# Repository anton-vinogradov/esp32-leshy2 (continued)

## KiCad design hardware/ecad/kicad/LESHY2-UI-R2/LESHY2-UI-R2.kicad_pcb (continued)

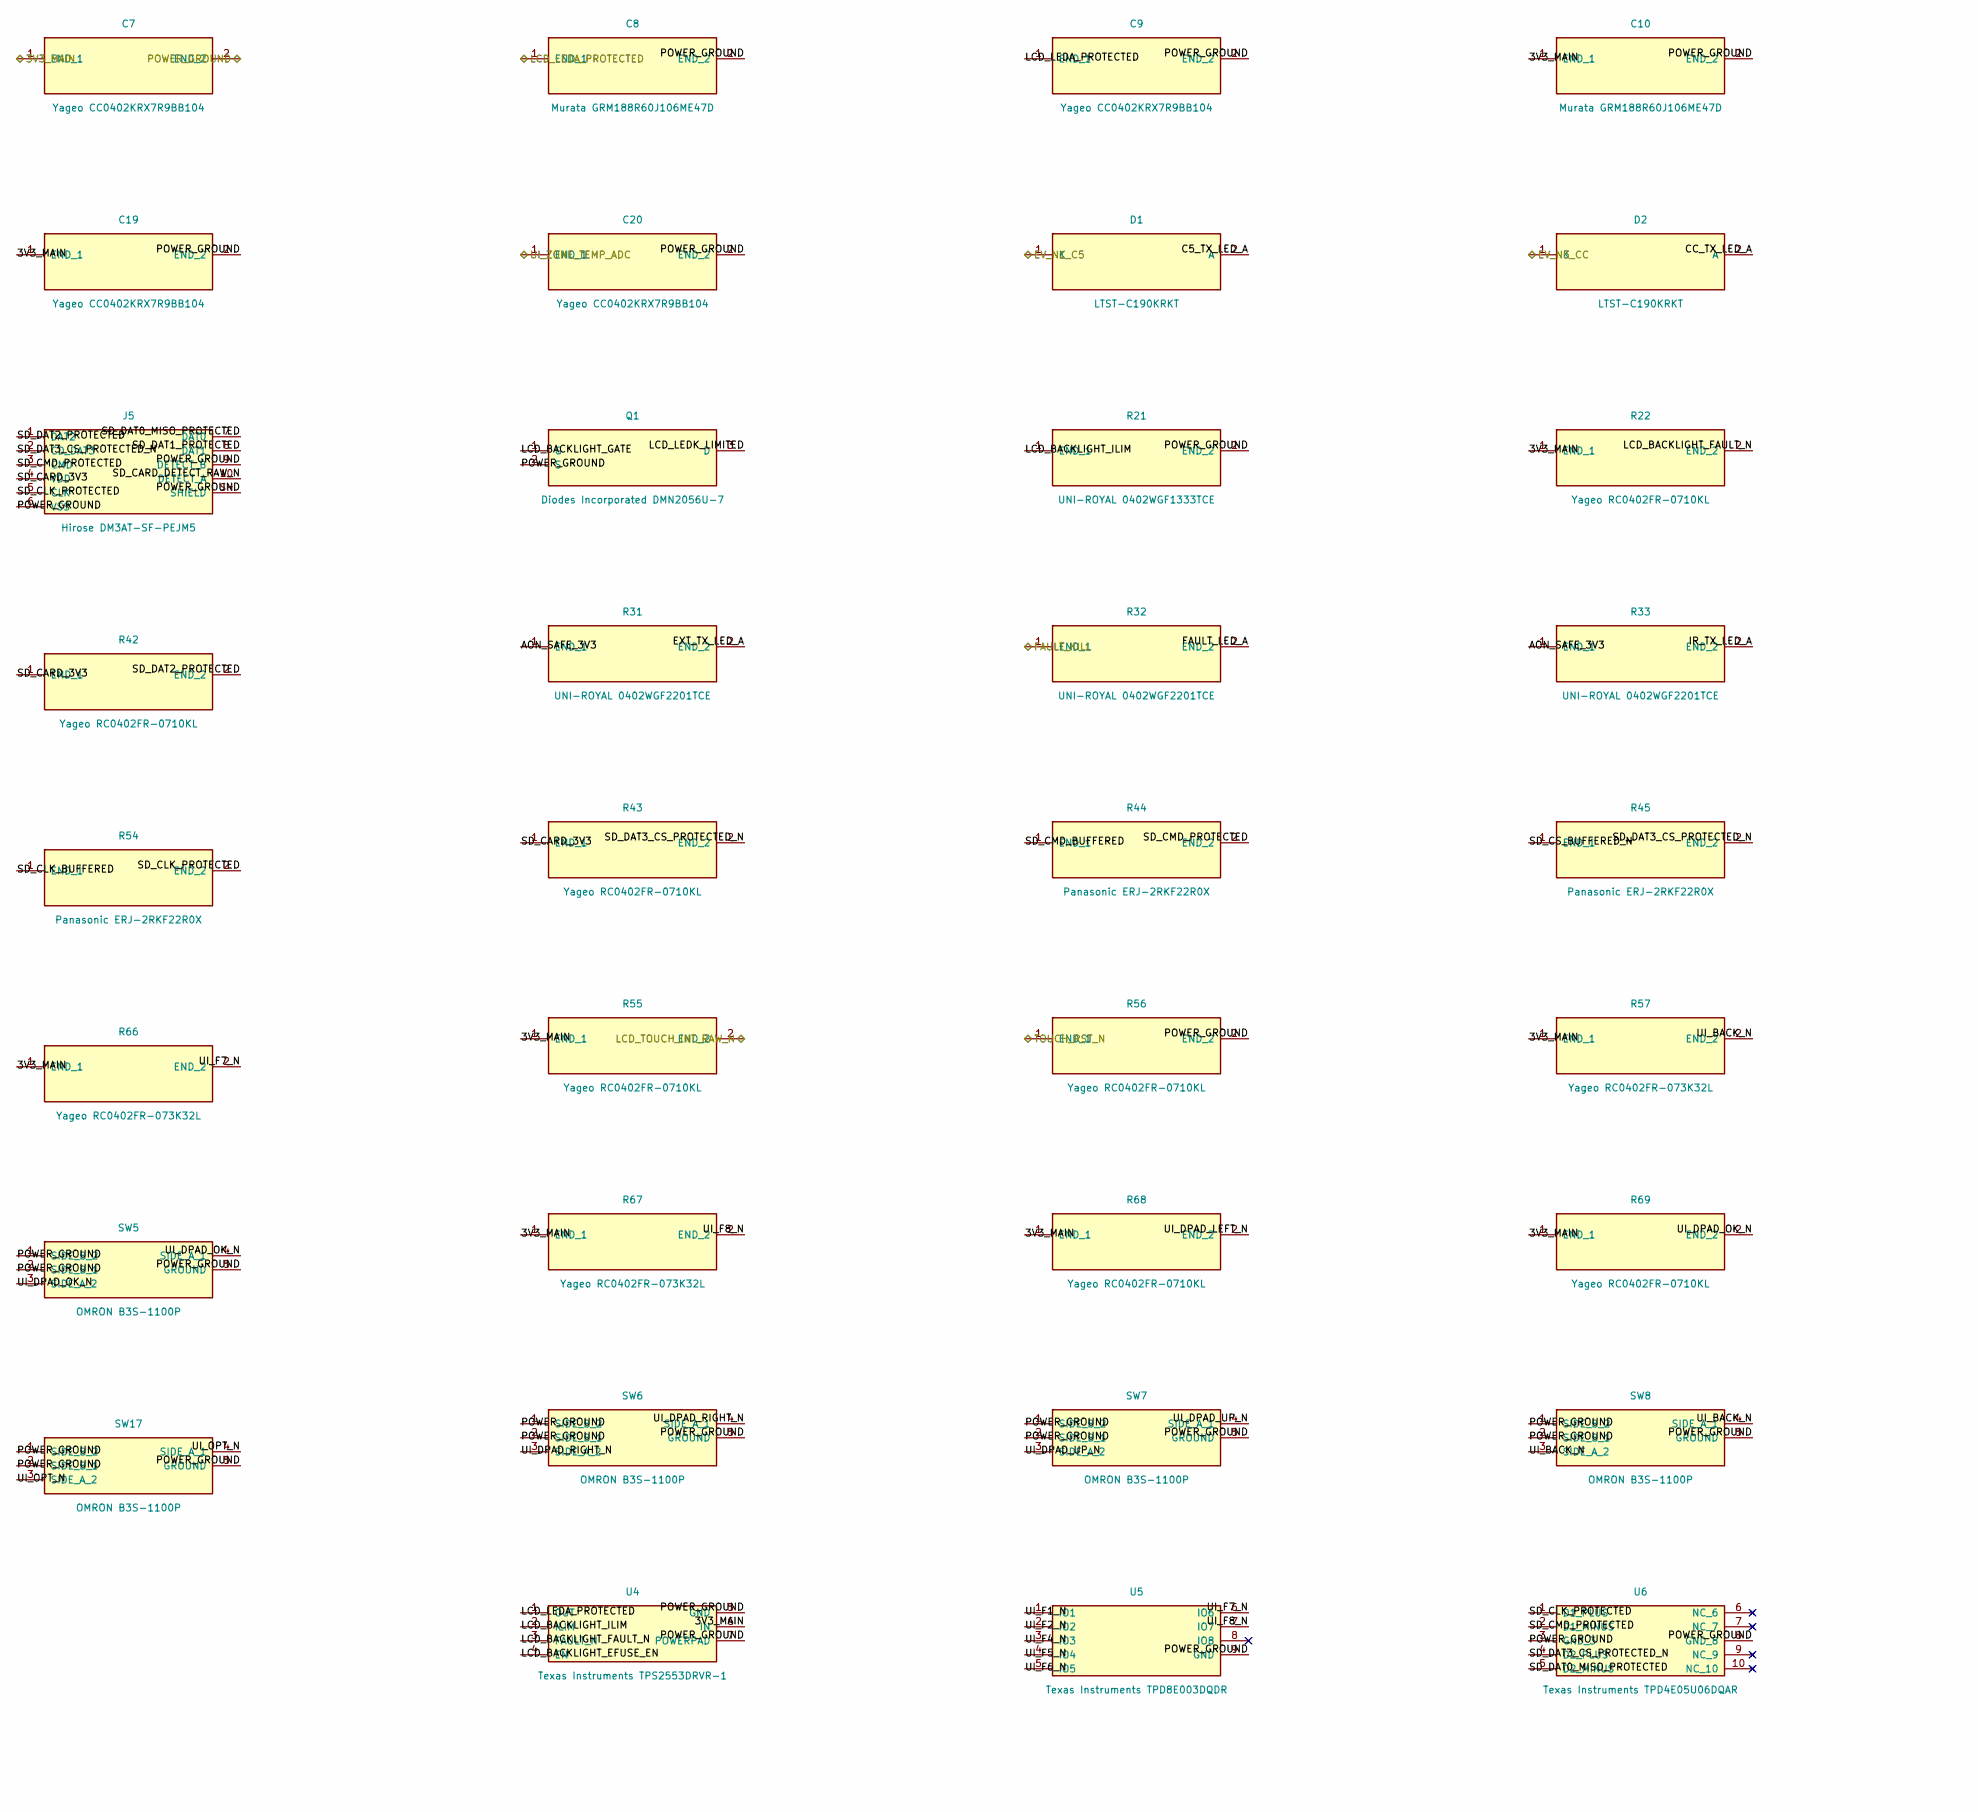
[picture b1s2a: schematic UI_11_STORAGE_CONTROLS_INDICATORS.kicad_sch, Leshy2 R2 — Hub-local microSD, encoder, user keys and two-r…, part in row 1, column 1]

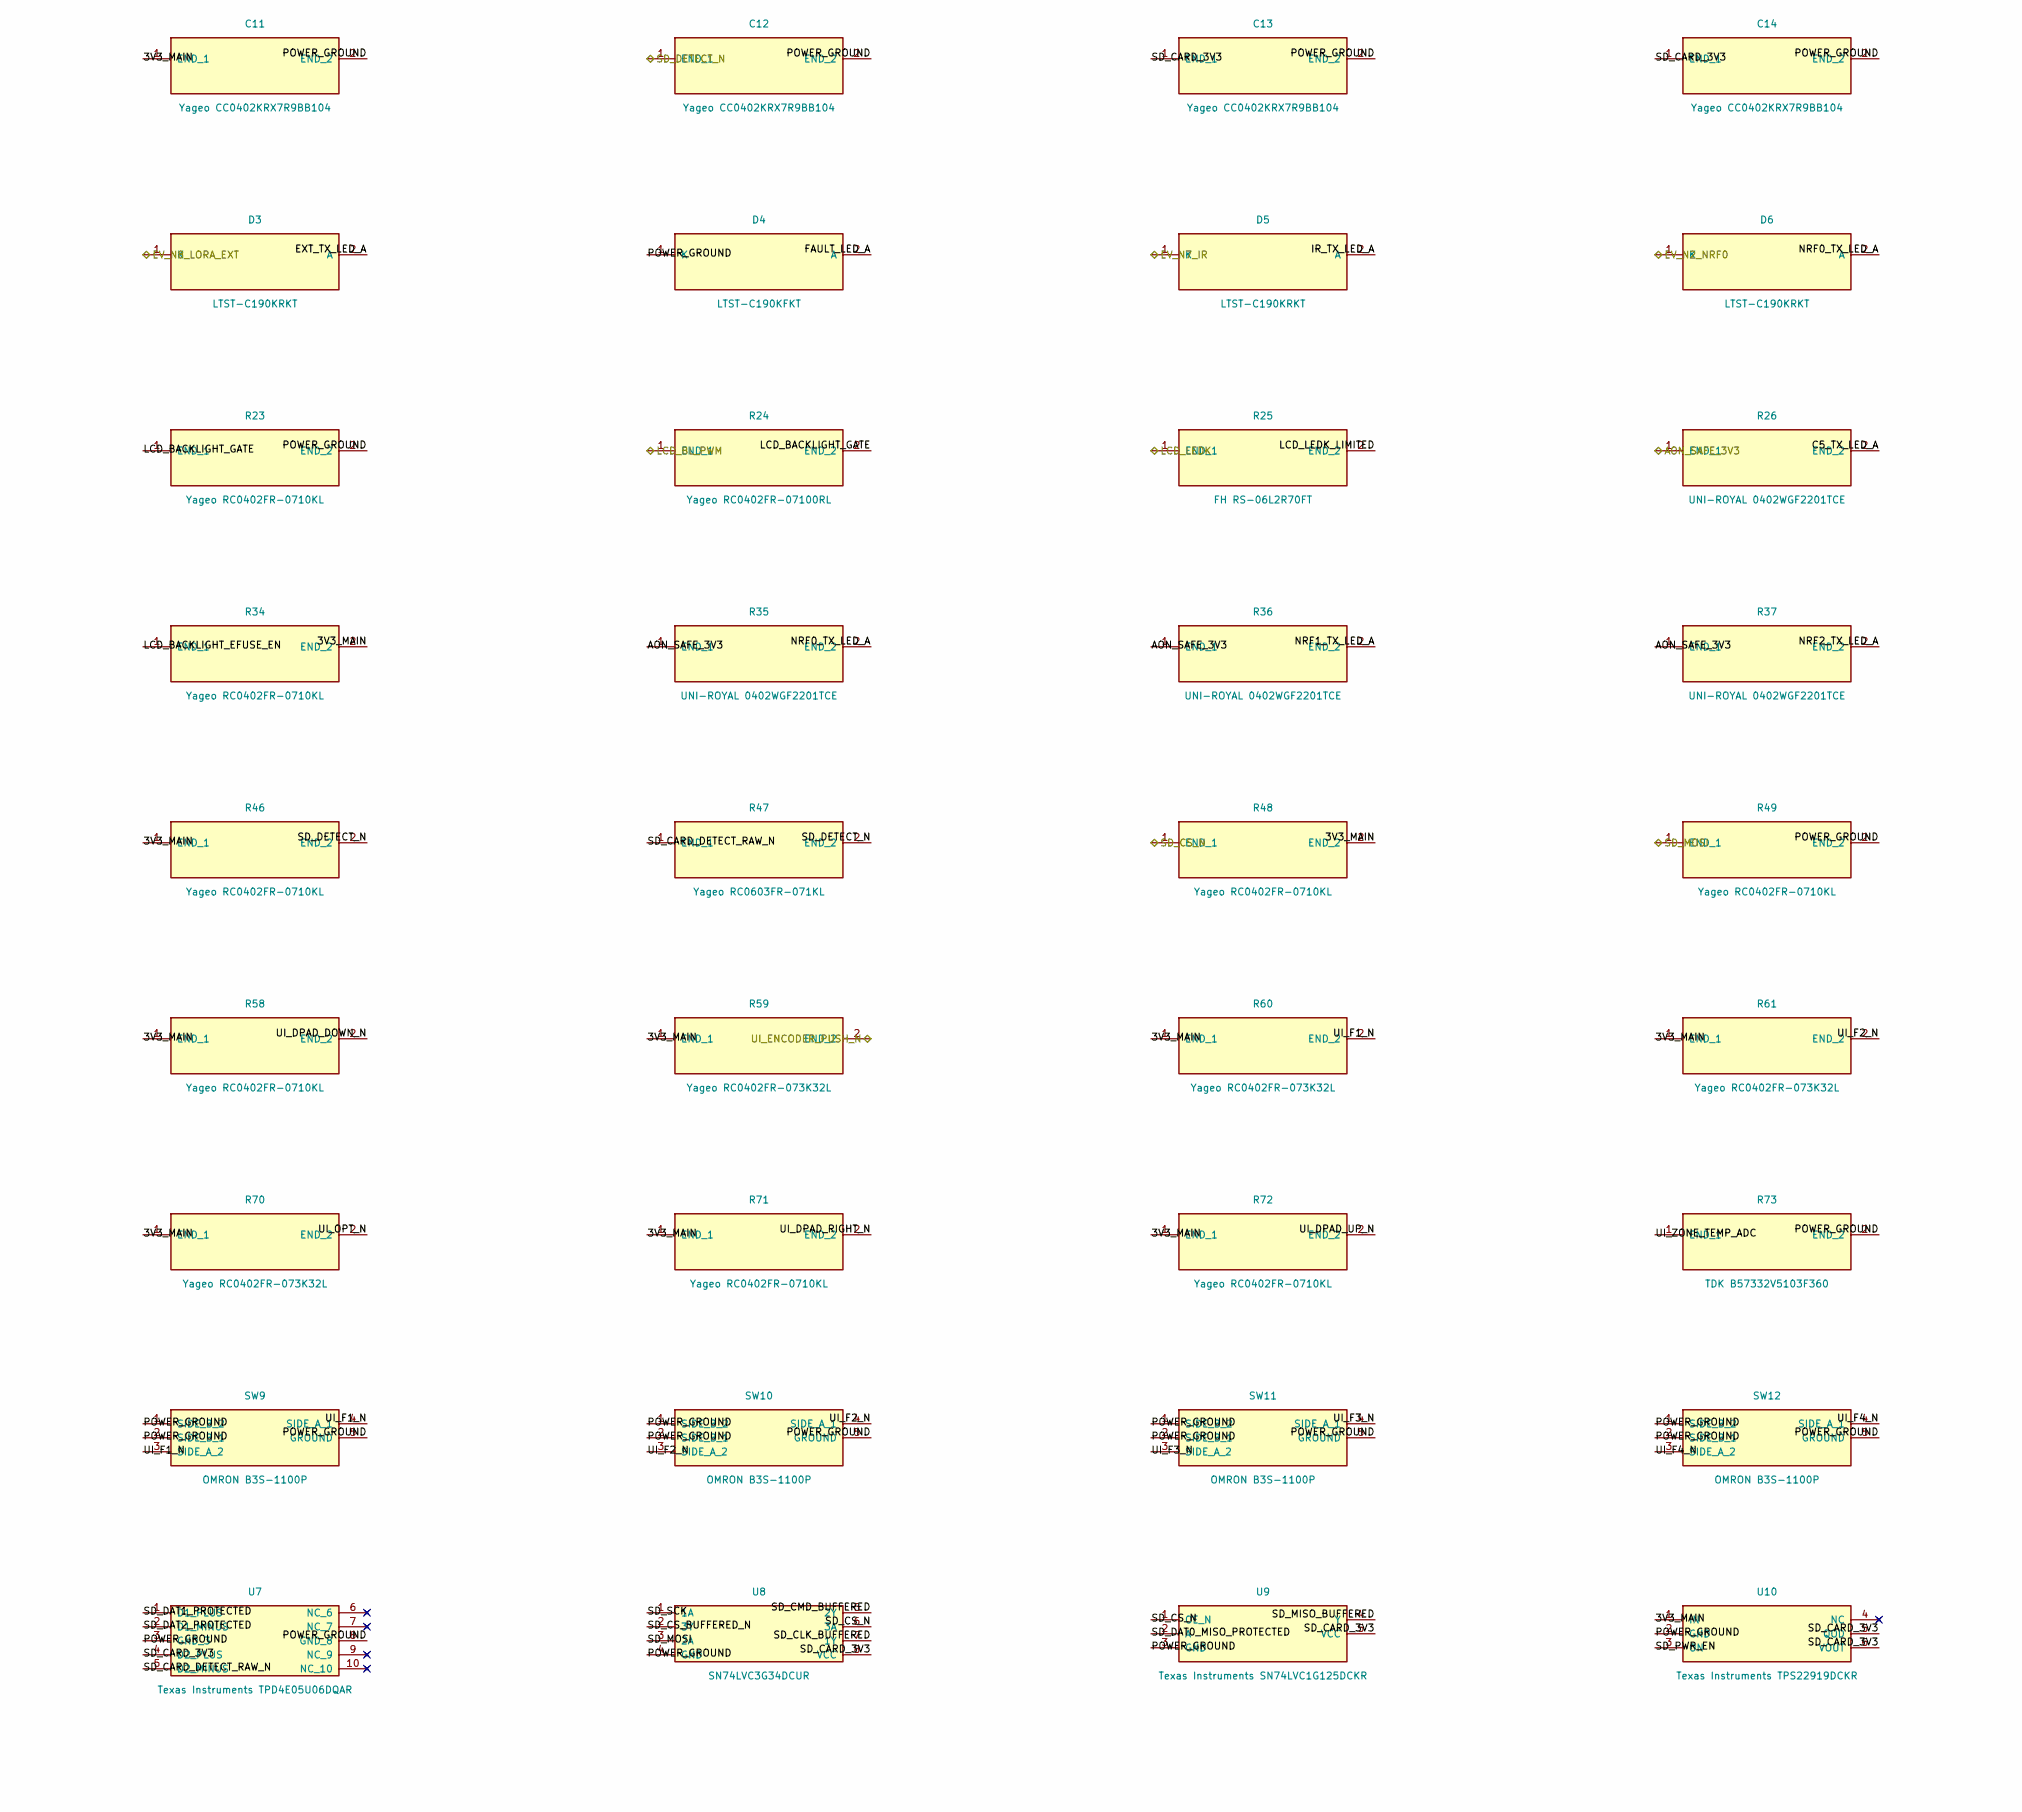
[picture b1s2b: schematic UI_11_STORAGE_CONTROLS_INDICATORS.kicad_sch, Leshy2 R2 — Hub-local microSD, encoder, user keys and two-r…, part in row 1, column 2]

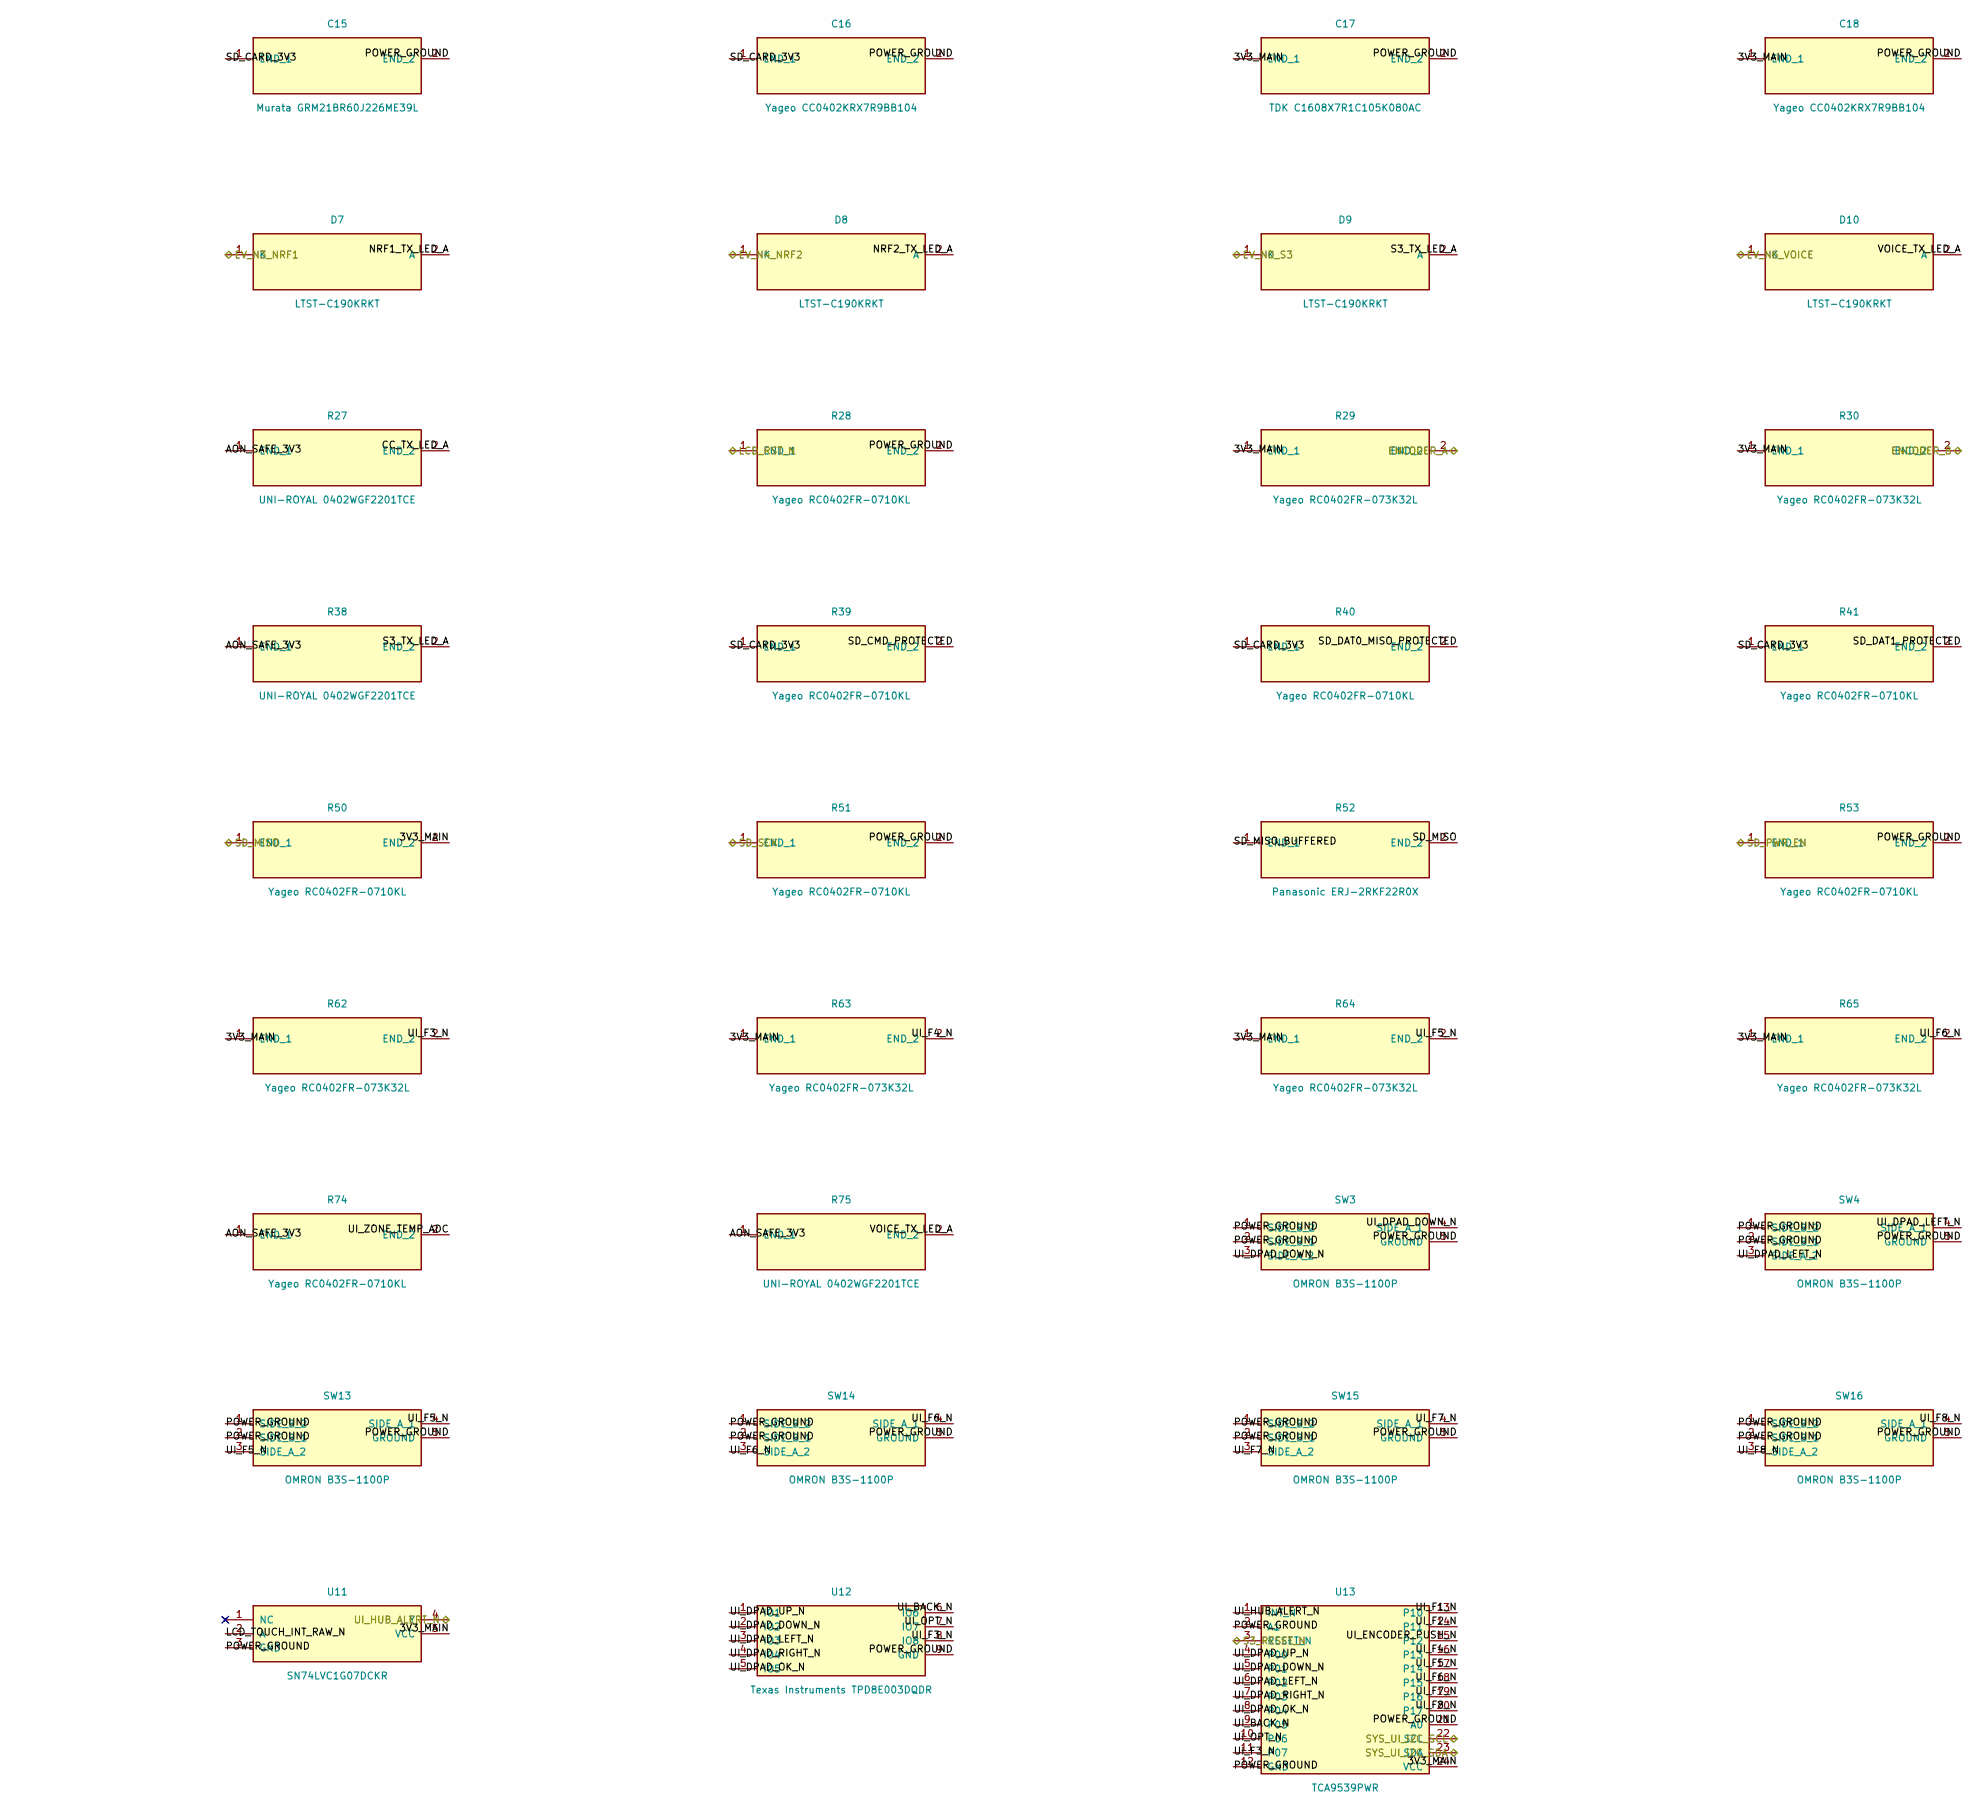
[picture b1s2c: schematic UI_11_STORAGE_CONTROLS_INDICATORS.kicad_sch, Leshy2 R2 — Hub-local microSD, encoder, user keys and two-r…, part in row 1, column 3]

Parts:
C7, C9, C11, C12, C13, C14, C16, C18, C19, C20: Yageo CC0402KRX7R9BB104; C_0402_1005Metric
C8, C10: Murata GRM188R60J106ME47D; C_0603_1608Metric
C15: Murata GRM21BR60J226ME39L; C_0805_2012Metric
C17: TDK C1608X7R1C105K080AC; C_0603_1608Metric
D1, D2, D3, D5, D6, D7, D8, D9, D10: LTST-C190KRKT; LED_0603_1608Metric
D4: LTST-C190KFKT; LED_0603_1608Metric
J5: Hirose DM3AT-SF-PEJM5; microSD_HC_Hirose_DM3AT-SF-PEJM5
Q1: Diodes Incorporated DMN2056U-7; SOT-23
R21: UNI-ROYAL 0402WGF1333TCE; R_0402_1005Metric
R22, R23, R28, R34, R39, R40, R41, R42, R43, R46, R48, R49, R50, R51, R53, R55, R56, R58, R68, R69, R71, R72, R74: Yageo RC0402FR-0710KL; R_0402_1005Metric
R24: Yageo RC0402FR-07100RL; R_0402_1005Metric
R25: FH RS-06L2R70FT; R_1206_3216Metric
R26, R27, R31, R32, R33, R35, R36, R37, R38, R75: UNI-ROYAL 0402WGF2201TCE; R_0402_1005Metric
R29, R30, R57, R59, R60, R61, R62, R63, R64, R65, R66, R67, R70: Yageo RC0402FR-073K32L; R_0402_1005Metric
R44, R45, R52, R54: Panasonic ERJ-2RKF22R0X; R_0402_1005Metric
R47: Yageo RC0603FR-071KL; R_0603_1608Metric
R73: TDK B57332V5103F360; R_0603_1608Metric
SW3, SW4, SW5, SW6, SW7, SW8, SW9, SW10, SW11, SW12, SW13, SW14, SW15, SW16, SW17: OMRON B3S-1100P; B3S-1100P
U4: Texas Instruments TPS2553DRVR-1; WSON-6-1EP_2x2mm_P0.65mm_EP1x1.6mm
U5, U12: Texas Instruments TPD8E003DQDR; TPD8E003DQDR
U6, U7: Texas Instruments TPD4E05U06DQAR; USON-10_2.5x1.0mm_P0.5mm
U8: SN74LVC3G34DCUR; VSSOP-8_2.3x2mm_P0.5mm
U9: Texas Instruments SN74LVC1G125DCKR; Texas_R-PDSO-G5_DCK-5
U10: Texas Instruments TPS22919DCKR; SOT-363_SC-70-6
U11: SN74LVC1G07DCKR; Texas_R-PDSO-G5_DCK-5
U13: TCA9539PWR; TSSOP-24_4.4x7.8mm_P0.65mm

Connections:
/UI_10_S3_DISPLAY_TOUCH/3V3_MAIN: C7.1 (END_1), C10.1 (END_1), C11.1 (END_1), C17.1 (END_1), C18.1 (END_1), C19.1 (END_1), R22.1 (END_1), R29.1 (END_1), R30.1 (END_1), R34.2 (END_2), R46.1 (END_1), R48.2 (END_2), R50.2 (END_2), R55.1 (END_1), R57.1 (END_1), R58.1 (END_1), R59.1 (END_1), R60.1 (END_1), R61.1 (END_1), R62.1 (END_1), R63.1 (END_1), R64.1 (END_1), R65.1 (END_1), R66.1 (END_1), R67.1 (END_1), R68.1 (END_1), R69.1 (END_1), R70.1 (END_1), R71.1 (END_1), R72.1 (END_1), U4.6 (IN), U10.1 (IN), U11.5 (VCC), U13.24 (VCC); also elsewhere on the board
/UI_10_S3_DISPLAY_TOUCH/AON_SAFE_3V3: R26.1 (END_1), R27.1 (END_1), R31.1 (END_1), R33.1 (END_1), R35.1 (END_1), R36.1 (END_1), R37.1 (END_1), R38.1 (END_1), R74.1 (END_1), R75.1 (END_1); also elsewhere on the board
/UI_10_S3_DISPLAY_TOUCH/ENCODER_A: R29.2 (END_2); also elsewhere on the board
/UI_10_S3_DISPLAY_TOUCH/ENCODER_B: R30.2 (END_2); also elsewhere on the board
/UI_10_S3_DISPLAY_TOUCH/LCD_LEDK: R25.1 (END_1); also elsewhere on the board
/UI_10_S3_DISPLAY_TOUCH/LCD_RST_N: R28.1 (END_1); also elsewhere on the board
/UI_10_S3_DISPLAY_TOUCH/POWER_GROUND: C7.2 (END_2), C8.2 (END_2), C9.2 (END_2), C10.2 (END_2), C11.2 (END_2), C12.2 (END_2), C13.2 (END_2), C14.2 (END_2), C15.2 (END_2), C16.2 (END_2), C17.2 (END_2), C18.2 (END_2), C19.2 (END_2), C20.2 (END_2), D4.1 (K), J5.6 (VSS), J5.9 (DETECT_B), J5.SH (SHIELD), Q1.2 (S), R21.2 (END_2), R23.2 (END_2), R28.2 (END_2), R49.2 (END_2), R51.2 (END_2), R53.2 (END_2), R56.2 (END_2), R73.2 (END_2), SW3.1 (SIDE_B_2), SW3.2 (SIDE_B_1), SW3.5 (GROUND), SW4.1 (SIDE_B_2), SW4.2 (SIDE_B_1), SW4.5 (GROUND), SW5.1 (SIDE_B_2), SW5.2 (SIDE_B_1), SW5.5 (GROUND), SW6.1 (SIDE_B_2), SW6.2 (SIDE_B_1), SW6.5 (GROUND), SW7.1 (SIDE_B_2), SW7.2 (SIDE_B_1), SW7.5 (GROUND), SW8.1 (SIDE_B_2), SW8.2 (SIDE_B_1), SW8.5 (GROUND), SW9.1 (SIDE_B_2), SW9.2 (SIDE_B_1), SW9.5 (GROUND), SW10.1 (SIDE_B_2), SW10.2 (SIDE_B_1), SW10.5 (GROUND), SW11.1 (SIDE_B_2), SW11.2 (SIDE_B_1), SW11.5 (GROUND), SW12.1 (SIDE_B_2), SW12.2 (SIDE_B_1), SW12.5 (GROUND), SW13.1 (SIDE_B_2), SW13.2 (SIDE_B_1), SW13.5 (GROUND), SW14.1 (SIDE_B_2), SW14.2 (SIDE_B_1), SW14.5 (GROUND), SW15.1 (SIDE_B_2), SW15.2 (SIDE_B_1), SW15.5 (GROUND), SW16.1 (SIDE_B_2), SW16.2 (SIDE_B_1), SW16.5 (GROUND), SW17.1 (SIDE_B_2), SW17.2 (SIDE_B_1), SW17.5 (GROUND), U4.5 (GND), U4.7 (POWERPAD), U5.9 (GND), U6.3 (GND_3), U6.8 (GND_8), U7.3 (GND_3), U7.8 (GND_8), U8.4 (GND), U9.3 (GND), U10.2 (GND), U11.3 (GND), U12.9 (GND), U13.2 (A1), U13.12 (GND), U13.21 (A0); also elsewhere on the board
/UI_10_S3_DISPLAY_TOUCH/S3_RESET_N: U13.3 (RESET_N); also elsewhere on the board
/UI_10_S3_DISPLAY_TOUCH/SYS_UI_I2C_SCL: U13.22 (SCL); also elsewhere on the board
/UI_10_S3_DISPLAY_TOUCH/SYS_UI_I2C_SDA: U13.23 (SDA); also elsewhere on the board
/UI_10_S3_DISPLAY_TOUCH/TOUCH_RST_N: R56.1 (END_1); also elsewhere on the board
/UI_10_S3_DISPLAY_TOUCH/UI_HUB_ALERT_N: U11.4 (Y), U13.1 (INT_N); also elsewhere on the board
/UI_11_STORAGE_CONTROLS_INDICATORS/C5_TX_LED_A: D1.2 (A), R26.2 (END_2)
/UI_11_STORAGE_CONTROLS_INDICATORS/CC_TX_LED_A: D2.2 (A), R27.2 (END_2)
/UI_11_STORAGE_CONTROLS_INDICATORS/EV_N5_CC: D2.1 (K); also elsewhere on the board
/UI_11_STORAGE_CONTROLS_INDICATORS/EV_N6_VOICE: D10.1 (K); also elsewhere on the board
/UI_11_STORAGE_CONTROLS_INDICATORS/EV_N8_LORA_EXT: D3.1 (K); also elsewhere on the board
/UI_11_STORAGE_CONTROLS_INDICATORS/EXT_TX_LED_A: D3.2 (A), R31.2 (END_2)
/UI_11_STORAGE_CONTROLS_INDICATORS/FAULT_KILL: R32.1 (END_1); also elsewhere on the board
/UI_11_STORAGE_CONTROLS_INDICATORS/FAULT_LED_A: D4.2 (A), R32.2 (END_2)
/UI_11_STORAGE_CONTROLS_INDICATORS/IR_TX_LED_A: D5.2 (A), R33.2 (END_2)
/UI_11_STORAGE_CONTROLS_INDICATORS/LCD_BACKLIGHT_EFUSE_EN: R34.1 (END_1), U4.4 (EN)
/UI_11_STORAGE_CONTROLS_INDICATORS/LCD_BACKLIGHT_FAULT_N: R22.2 (END_2), U4.3 (FAULT_N)
/UI_11_STORAGE_CONTROLS_INDICATORS/LCD_BACKLIGHT_GATE: Q1.1 (G), R23.1 (END_1), R24.2 (END_2)
/UI_11_STORAGE_CONTROLS_INDICATORS/LCD_BACKLIGHT_ILIM: R21.1 (END_1), U4.2 (ILIM)
/UI_11_STORAGE_CONTROLS_INDICATORS/LCD_BL_PWM: R24.1 (END_1); also elsewhere on the board
/UI_11_STORAGE_CONTROLS_INDICATORS/LCD_LEDA_PROTECTED: C8.1 (END_1), C9.1 (END_1), U4.1 (OUT); also elsewhere on the board
/UI_11_STORAGE_CONTROLS_INDICATORS/LCD_LEDK_LIMITED: Q1.3 (D), R25.2 (END_2)
/UI_11_STORAGE_CONTROLS_INDICATORS/LCD_TOUCH_INT_RAW_N: R55.2 (END_2), U11.2 (A); also elsewhere on the board
/UI_11_STORAGE_CONTROLS_INDICATORS/NRF0_TX_LED_A: D6.2 (A), R35.2 (END_2)
/UI_11_STORAGE_CONTROLS_INDICATORS/NRF1_TX_LED_A: D7.2 (A), R36.2 (END_2)
/UI_11_STORAGE_CONTROLS_INDICATORS/NRF2_TX_LED_A: D8.2 (A), R37.2 (END_2)
/UI_11_STORAGE_CONTROLS_INDICATORS/S3_TX_LED_A: D9.2 (A), R38.2 (END_2)
/UI_11_STORAGE_CONTROLS_INDICATORS/SD_CARD_3V3: C13.1 (END_1), C14.1 (END_1), C15.1 (END_1), C16.1 (END_1), J5.4 (VDD), R39.1 (END_1), R40.1 (END_1), R41.1 (END_1), R42.1 (END_1), R43.1 (END_1), U7.4 (D2_PLUS), U8.8 (VCC), U9.5 (VCC), U10.5 (QOD), U10.6 (VOUT)
/UI_11_STORAGE_CONTROLS_INDICATORS/SD_CARD_DETECT_RAW_N: J5.10 (DETECT_A), R47.1 (END_1), U7.5 (D2_MINUS)
/UI_11_STORAGE_CONTROLS_INDICATORS/SD_CLK_BUFFERED: R54.1 (END_1), U8.7 (1Y)
/UI_11_STORAGE_CONTROLS_INDICATORS/SD_CLK_PROTECTED: J5.5 (CLK), R54.2 (END_2), U6.1 (D1_PLUS)
/UI_11_STORAGE_CONTROLS_INDICATORS/SD_CMD_BUFFERED: R44.1 (END_1), U8.5 (2Y)
/UI_11_STORAGE_CONTROLS_INDICATORS/SD_CMD_PROTECTED: J5.3 (CMD), R39.2 (END_2), R44.2 (END_2), U6.2 (D1_MINUS)
/UI_11_STORAGE_CONTROLS_INDICATORS/SD_CS_BUFFERED_N: R45.1 (END_1), U8.2 (3Y)
/UI_11_STORAGE_CONTROLS_INDICATORS/SD_CS_N: R48.1 (END_1), U8.6 (3A), U9.1 (OE_N); also elsewhere on the board
/UI_11_STORAGE_CONTROLS_INDICATORS/SD_DAT0_MISO_PROTECTED: J5.7 (DAT0), R40.2 (END_2), U6.5 (D2_MINUS), U9.2 (A)
/UI_11_STORAGE_CONTROLS_INDICATORS/SD_DAT1_PROTECTED: J5.8 (DAT1), R41.2 (END_2), U7.1 (D1_PLUS)
/UI_11_STORAGE_CONTROLS_INDICATORS/SD_DAT2_PROTECTED: J5.1 (DAT2), R42.2 (END_2), U7.2 (D1_MINUS)
/UI_11_STORAGE_CONTROLS_INDICATORS/SD_DAT3_CS_PROTECTED_N: J5.2 (CD_DAT3), R43.2 (END_2), R45.2 (END_2), U6.4 (D2_PLUS)
/UI_11_STORAGE_CONTROLS_INDICATORS/SD_DETECT_N: C12.1 (END_1), R46.2 (END_2), R47.2 (END_2); also elsewhere on the board
/UI_11_STORAGE_CONTROLS_INDICATORS/SD_MISO: R50.1 (END_1), R52.2 (END_2); also elsewhere on the board
/UI_11_STORAGE_CONTROLS_INDICATORS/SD_MISO_BUFFERED: R52.1 (END_1), U9.4 (Y)
/UI_11_STORAGE_CONTROLS_INDICATORS/SD_MOSI: R49.1 (END_1), U8.3 (2A); also elsewhere on the board
/UI_11_STORAGE_CONTROLS_INDICATORS/SD_PWR_EN: R53.1 (END_1), U10.3 (ON); also elsewhere on the board
/UI_11_STORAGE_CONTROLS_INDICATORS/SD_SCK: R51.1 (END_1), U8.1 (1A); also elsewhere on the board
/UI_11_STORAGE_CONTROLS_INDICATORS/UI_BACK_N: R57.2 (END_2), SW8.3 (SIDE_A_2), SW8.4 (SIDE_A_1), U12.6 (IO6), U13.9 (P05)
/UI_11_STORAGE_CONTROLS_INDICATORS/UI_DPAD_DOWN_N: R58.2 (END_2), SW3.3 (SIDE_A_2), SW3.4 (SIDE_A_1), U12.2 (IO2), U13.5 (P01)
/UI_11_STORAGE_CONTROLS_INDICATORS/UI_DPAD_LEFT_N: R68.2 (END_2), SW4.3 (SIDE_A_2), SW4.4 (SIDE_A_1), U12.3 (IO3), U13.6 (P02)
/UI_11_STORAGE_CONTROLS_INDICATORS/UI_DPAD_OK_N: R69.2 (END_2), SW5.3 (SIDE_A_2), SW5.4 (SIDE_A_1), U12.5 (IO5), U13.8 (P04)
/UI_11_STORAGE_CONTROLS_INDICATORS/UI_DPAD_RIGHT_N: R71.2 (END_2), SW6.3 (SIDE_A_2), SW6.4 (SIDE_A_1), U12.4 (IO4), U13.7 (P03)
/UI_11_STORAGE_CONTROLS_INDICATORS/UI_DPAD_UP_N: R72.2 (END_2), SW7.3 (SIDE_A_2), SW7.4 (SIDE_A_1), U12.1 (IO1), U13.4 (P00)
/UI_11_STORAGE_CONTROLS_INDICATORS/UI_ENCODER_PUSH_N: R59.2 (END_2), U13.15 (P12); also elsewhere on the board
/UI_11_STORAGE_CONTROLS_INDICATORS/UI_F1_N: R60.2 (END_2), SW9.3 (SIDE_A_2), SW9.4 (SIDE_A_1), U5.1 (IO1), U13.13 (P10)
/UI_11_STORAGE_CONTROLS_INDICATORS/UI_F2_N: R61.2 (END_2), SW10.3 (SIDE_A_2), SW10.4 (SIDE_A_1), U5.2 (IO2), U13.14 (P11)
/UI_11_STORAGE_CONTROLS_INDICATORS/UI_F3_N: R62.2 (END_2), SW11.3 (SIDE_A_2), SW11.4 (SIDE_A_1), U12.8 (IO8), U13.11 (P07)
/UI_11_STORAGE_CONTROLS_INDICATORS/UI_F4_N: R63.2 (END_2), SW12.3 (SIDE_A_2), SW12.4 (SIDE_A_1), U5.3 (IO3), U13.16 (P13)
/UI_11_STORAGE_CONTROLS_INDICATORS/UI_F5_N: R64.2 (END_2), SW13.3 (SIDE_A_2), SW13.4 (SIDE_A_1), U5.4 (IO4), U13.17 (P14)
/UI_11_STORAGE_CONTROLS_INDICATORS/UI_F6_N: R65.2 (END_2), SW14.3 (SIDE_A_2), SW14.4 (SIDE_A_1), U5.5 (IO5), U13.18 (P15)
/UI_11_STORAGE_CONTROLS_INDICATORS/UI_F7_N: R66.2 (END_2), SW15.3 (SIDE_A_2), SW15.4 (SIDE_A_1), U5.6 (IO6), U13.19 (P16)
/UI_11_STORAGE_CONTROLS_INDICATORS/UI_F8_N: R67.2 (END_2), SW16.3 (SIDE_A_2), SW16.4 (SIDE_A_1), U5.7 (IO7), U13.20 (P17)
/UI_11_STORAGE_CONTROLS_INDICATORS/UI_OPT_N: R70.2 (END_2), SW17.3 (SIDE_A_2), SW17.4 (SIDE_A_1), U12.7 (IO7), U13.10 (P06)
/UI_11_STORAGE_CONTROLS_INDICATORS/UI_ZONE_TEMP_ADC: C20.1 (END_1), R73.1 (END_1), R74.2 (END_2); also elsewhere on the board
/UI_11_STORAGE_CONTROLS_INDICATORS/VOICE_TX_LED_A: D10.2 (A), R75.2 (END_2)
/UI_20_C5_WIFI_IR_SERVICE/EV_N1_C5: D1.1 (K); also elsewhere on the board
/UI_20_C5_WIFI_IR_SERVICE/EV_N7_IR: D5.1 (K); also elsewhere on the board
/UI_50_FRONT_POWER_SAFETY/EV_N0_S3: D9.1 (K); also elsewhere on the board
/UI_50_FRONT_POWER_SAFETY/EV_N2_NRF0: D6.1 (K); also elsewhere on the board
/UI_50_FRONT_POWER_SAFETY/EV_N3_NRF1: D7.1 (K); also elsewhere on the board
/UI_50_FRONT_POWER_SAFETY/EV_N4_NRF2: D8.1 (K); also elsewhere on the board
